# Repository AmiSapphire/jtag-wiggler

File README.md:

This project was originally for my own private personal use, but I am deciding to make this a repository anyway.

This is also my first time using vias on a PCB layout! Oh, this was made with KiCAD 7.0, so any earlier release will not work.

The circuit was tested with a 74HC244 IC and TJTAG 3.0.1 and 3.0.2.1 on a few machines with success barring issues with using one 74HC244; replacing it with another 74HC244 from the same set fixed the recognition issue. This is why a 74HCT244 is recommended with this circuit.

--

This same circuit on a perfboard - prototype unit before the final PCB design... photos aren't as clear; my long retired LG G7 ThinQ was better for this.
Also, the jumpers for switching 3V3/5V0 exist because I do not have a DPDT switch on hand.

Top view

Bottom view

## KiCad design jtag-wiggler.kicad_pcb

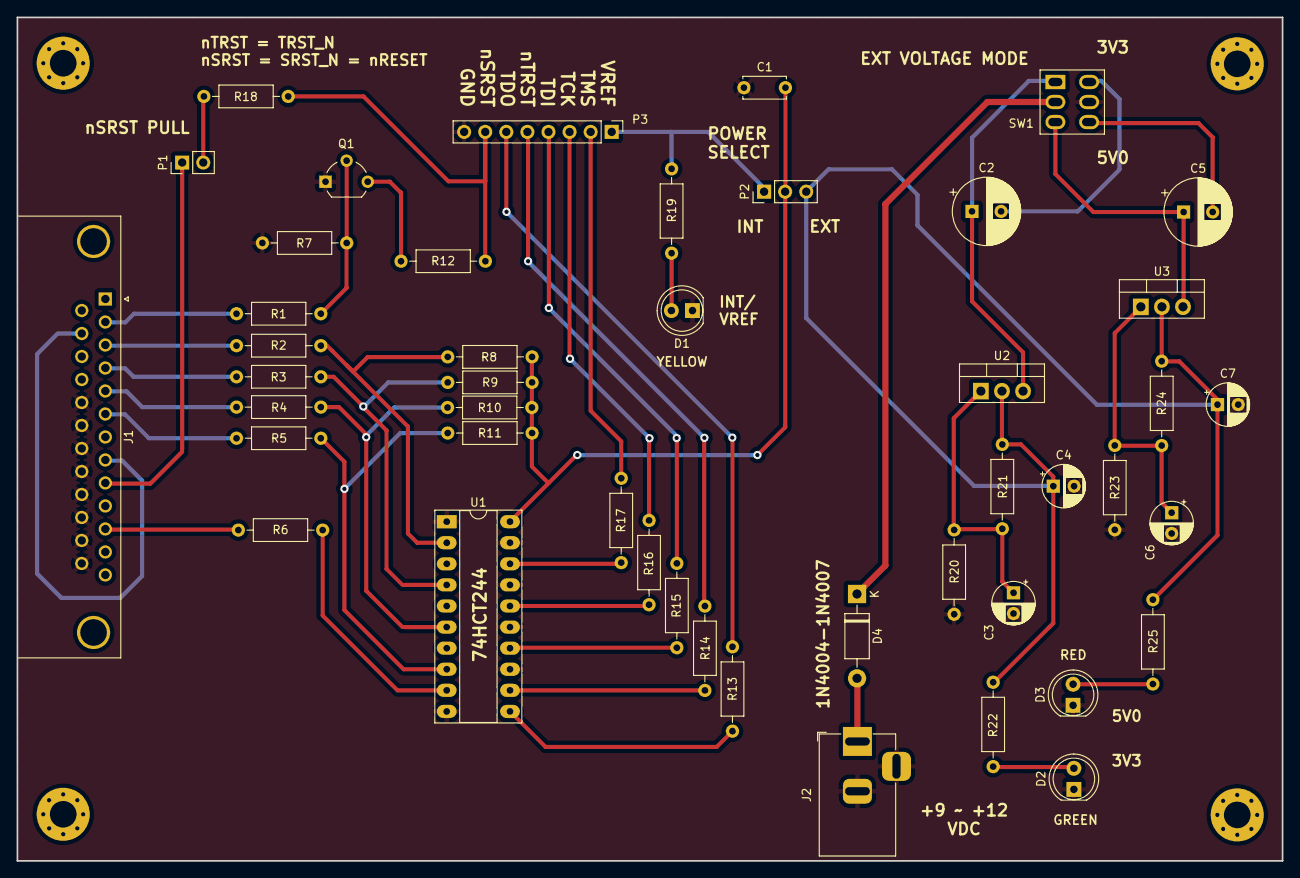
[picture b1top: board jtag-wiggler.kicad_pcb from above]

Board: 2 copper layers, 152.4 x 101.6 mm, 50 parts (0 on the bottom side), 42 nets.

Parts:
C1: C_Disc_D5.0mm_W2.5mm_P5.00mm
C2, C5: CP_Radial_D8.0mm_P3.50mm
C3, C4, C6, C7: CP_Radial_D5.0mm_P2.50mm
D1, D2, D3: LED_D5.0mm
D4: D_DO-41_SOD81_P10.16mm_Horizontal
J1: DSUB-25_Male_Horizontal_P2.77x2.84mm_EdgePinOffse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; DSUB-25_Male_Horizontal_P2.77x2.84mm_EdgePinOffset7.70mm_Ho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
J2: BarrelJack_Horizontal
P1: PinHeader_1x02_P2.54mm_Vertical
P2: PinHeader_1x03_P2.54mm_Vertical
P3: PinHeader_1x08_P2.54mm_Vertical
Q1: TO-92_Wide
R1, R2, R3, R4, R5, R6, R7, R8, R9, R10, R11, R12, R13, R14, R15, R16, R17, R18, R19, R20, R21, R22, R23, R24, R25: R_Axial_DIN0207_L6.3mm_D2.5mm_P10.16mm_Horizontal
SW1: SW_Generic
U1: DIP-20_W7.62mm_Socket_LongPads
U2, U3: TO-220-3_Vertical
X1, X2, X3, X4: MountingHole_3.2mm_M3_Pad_Via

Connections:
/PSU_In: C4.1, C7.1, P2.3, R21.1, R22.1, R24.1, R25.1, U2.2, U3.2
/PWR_SELECT: C1.2, P2.2, R8.1, R9.1, R10.1, R11.1, U1.20
BUSY: J1.11, R6.1
C2_negative: C2.2, SW1.6
C2_positive: C2.1, SW1.1, U2.3
C5_negative: C5.2, SW1.4
C5_positive: C5.1, SW1.3, U3.3
D1: J1.2, R1.1
D2: J1.3, R2.1
D3: J1.4, R3.1
D4: J1.5, R4.1
D5: J1.6, R5.1
ERROR: J1.8, J1.15
GND: C1.1, C3.2, C4.2, C6.2, C7.2, D1.1, D2.1, D3.1, J1.18, J1.19, J1.20, J1.21, J1.22, J1.23, J1.24, J1.25, J2.2, J2.3, P3.8, Q1.1, R7.2, R20.2, R23.2, SW1.5, U1.1, U1.10, U1.13, U1.15, U1.17, U1.19
unnamed: D1.2, R19.1
unnamed: D2.2, R22.2
unnamed: D3.2, R25.2
unnamed: P1.2, R18.2
unnamed: Q1.2, R1.2, R7.1
unnamed: Q1.3, R12.1
unnamed: R2.2, R8.2, U1.2
unnamed: R3.2, R9.2, U1.4
unnamed: R4.2, R10.2, U1.6
unnamed: R5.2, R11.2, U1.8
unnamed: R17.1, U1.18
unnamed: R16.1, U1.16
unnamed: R15.1, U1.14
unnamed: R14.1, U1.12
unnamed: R13.1, U1.11
unnamed: R6.2, U1.9
unnamed: C3.1, R20.1, R21.2, U2.1
unnamed: C6.1, R23.1, R24.2, U3.1
PC_VCC: J1.9, P1.1
Protected_VCC: D4.1, SW1.2
TCK: P3.3, R16.2
TDI: P3.4, R15.2
TDO: P3.6, R13.2
TMS: P3.2, R17.2
VCC: D4.2, J2.1
VREF: P2.1, P3.1, R19.2
nSRST: P3.7, R12.2, R18.1
nTRST: P3.5, R14.2

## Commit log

2023-06-09 Update README.md
    Add top view of prototype circuit design. Remind self to take a photo of the bottom view later.
2023-06-09 Update README.md
    Previous commit also fixes TJTAG version typo. Current commit adds a bottom view photo and adds some detail regarding the jumpers on the prototype circuit.
2023-06-09 Needed for TI 74HCT244 variant pinout (custom)
2023-06-09 Add custom switch footprint; update PCB layout
2023-06-09 Update BOM to specify switch pin spacing
2023-06-09 Specify SW1 as 'Sub-miniature DPDT switch'
2023-06-09 Update SW1 footprint; fits up to 1.5mm pin width
2023-06-09 Specify KiCAD ver., because this is important
2023-06-12 Change SW1 footprint to 1.0mm vertical
2023-06-14 Remove extra track from D2; general PCB cleanup
2023-06-14 Add European standard PCB and reference
2023-06-14 Rev number bump, add comment for US/Euro Standard
